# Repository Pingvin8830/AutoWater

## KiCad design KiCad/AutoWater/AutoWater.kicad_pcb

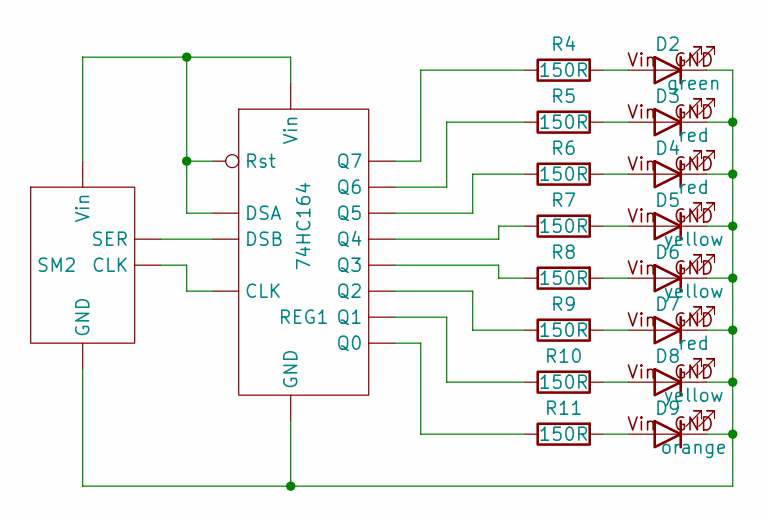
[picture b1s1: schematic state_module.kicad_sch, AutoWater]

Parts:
D2: green; LED 3mm
D3, D4, D7: red; LED 3mm
D5, D6, D8: yellow; LED 3mm
D9: orange; LED 3mm
R4, R5, R6, R7, R8, R9, R10, R11: 150R; Resistor Yageo SMD 1206
REG1: 74HC164; Register 74HC164M SOP-14
SM2: PLS-4

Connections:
unnamed: D2.Vin, R4.2
unnamed: D3.Vin, R5.2
unnamed: D4.Vin, R6.2
unnamed: D5.Vin, R7.2
unnamed: D6.Vin, R8.2
unnamed: D7.Vin, R9.2
unnamed: D8.Vin, R10.2
unnamed: D9.Vin, R11.2
unnamed: R4.1, REG1.Q7
unnamed: R5.1, REG1.Q6
unnamed: R6.1, REG1.Q5
unnamed: R7.1, REG1.Q4
unnamed: R8.1, REG1.Q3
unnamed: R9.1, REG1.Q2
unnamed: R10.1, REG1.Q1
unnamed: R11.1, REG1.Q0
unnamed: REG1.CLK, SM2.3 (CLK)
unnamed: D2.GND, D3.GND, D4.GND, D5.GND, D6.GND, D7.GND, D8.GND, D9.GND, REG1.GND, SM2.4 (GND)
unnamed: REG1.DSB, SM2.2 (SER)
unnamed: REG1.DSA, REG1.Rst, REG1.Vin, SM2.1 (Vin)

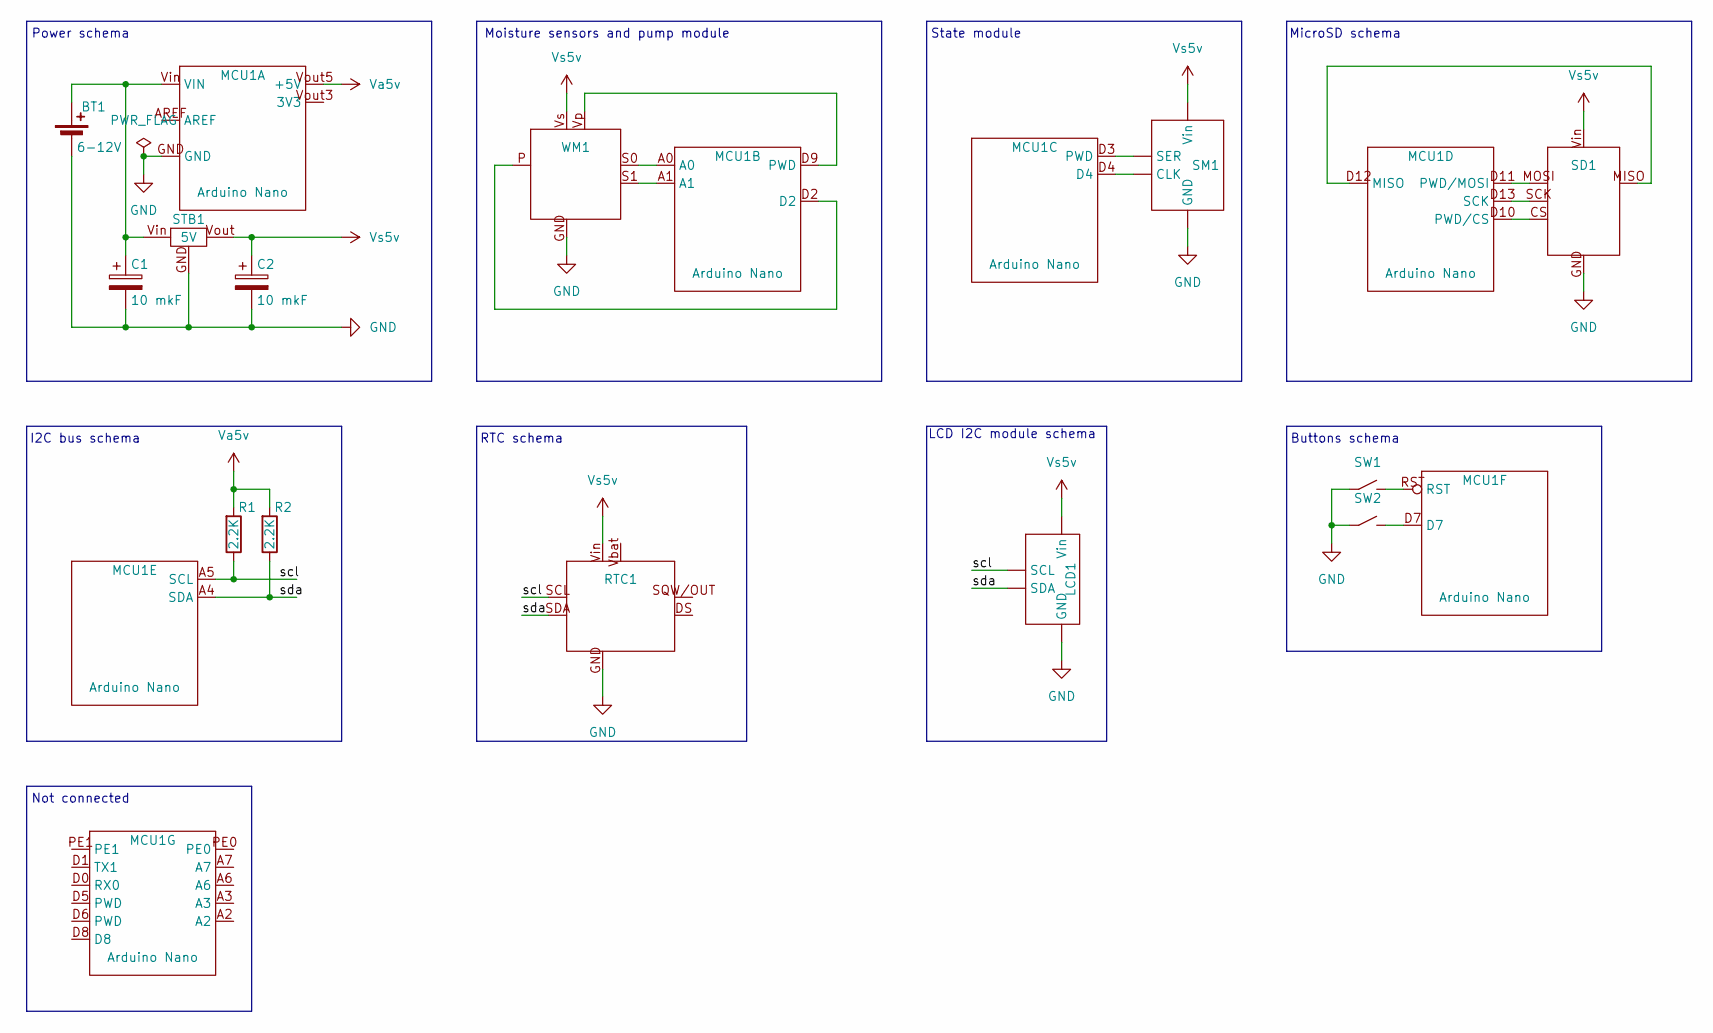
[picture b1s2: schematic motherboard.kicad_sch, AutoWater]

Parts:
BT1: 6-12V; Connector 5.5x2.1 DS-201
C1, C2: 10 mkF; Capacitor Murata SMD 0603
LCD1: LCD I2C module; PLS-4
MCU1: Arduino Nano; Arduino Nano V3 Type C PBS
R1, R2: 2.2K; Resistor Yageo SMD 1206
RTC1: RTC DS1307 module
SD1: MicroSD module
SM1: PLS-4
STB1: 5V; Stabilizer 5V AMS1117-5.0S SMD
SW1, SW2: Button; Connector B2B-XH-A
WM1: PLS-2x3

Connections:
/Motherboard/scl: LCD1.1 (SCL), MCU1.A5 (SCL), R1.1, RTC1.SCL
/Motherboard/sda: LCD1.2 (SDA), MCU1.A4 (SDA), R2.1, RTC1.SDA
GND: BT1.GND (-), C1.GND, C2.GND, LCD1.4 (GND), MCU1.GND, RTC1.GND, SD1.GND, SM1.4 (GND), STB1.GND, SW1.GND (1), SW2.GND (1), WM1.GND
unnamed: BT1.Vout (+), C1.Vin (VCC), MCU1.Vin (VIN), STB1.Vin
unnamed: MCU1.A0, WM1.S0
unnamed: MCU1.A1, WM1.S1
unnamed: MCU1.D2, WM1.P
unnamed: MCU1.D9 (PWD), WM1.Vp
unnamed: MCU1.D3 (PWD), SM1.2 (SER)
unnamed: MCU1.D12 (MISO), SD1.MISO
unnamed: MCU1.D10 (PWD/CS), SD1.CS
unnamed: MCU1.D11 (PWD/MOSI), SD1.MOSI
unnamed: MCU1.D13 (SCK), SD1.SCK
unnamed: MCU1.D4, SM1.3 (CLK)
unnamed: MCU1.RST, SW1.Vin (2)
unnamed: MCU1.D7, SW2.Vin (2)
Va5v: MCU1.Vout5 (+5V), R1.2, R2.2
Vs5v: C2.Vin (VCC), LCD1.3 (Vin), RTC1.Vin, SD1.Vin, SM1.1 (Vin), STB1.Vout, WM1.Vs

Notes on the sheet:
Power schema
LCD I2C module schema
I2C bus schema
Not connected
State module
MicroSD schema
Moisture sensors and pump module
Buttons schema
RTC schema

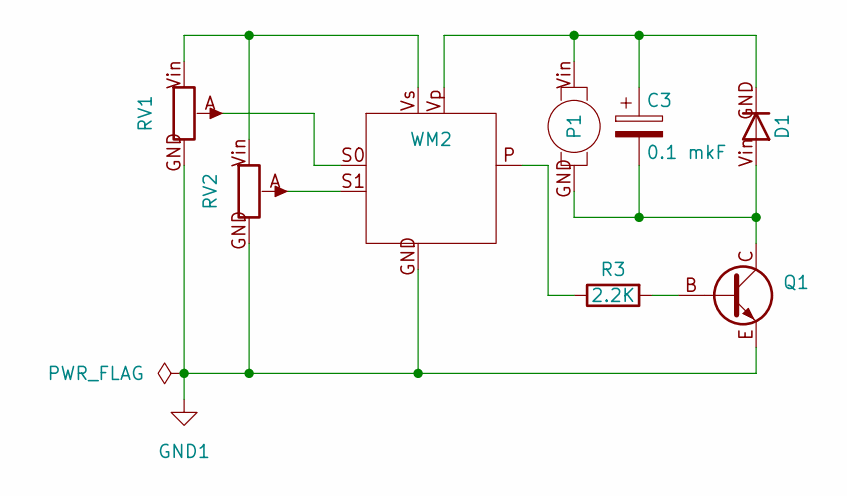
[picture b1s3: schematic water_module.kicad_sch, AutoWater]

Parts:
C3: 0.1 mkF; Capacitor Murata SMD 0402
D1: 1N4001G; DIode 1N4001G THT min
P1: Pump; Connector B2B-XH-A
Q1: BC817-25; NPN transistor BC817-25
R3: 2.2K; Resistor Yageo SMD 1206
RV1, RV2: PLS-3
WM2: PLS-2x3

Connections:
GND1: Q1.E, RV1.GND, RV2.GND, WM2.GND
unnamed: C3.Vin (VCC), D1.GND (K), P1.Vin (VCC), WM2.Vp
unnamed: C3.GND, D1.Vin (A), P1.GND, Q1.C
unnamed: Q1.B, R3.2
unnamed: R3.1, WM2.P
unnamed: RV1.A, WM2.S0
unnamed: RV1.Vin (VCC), RV2.Vin (VCC), WM2.Vs
unnamed: RV2.A, WM2.S1

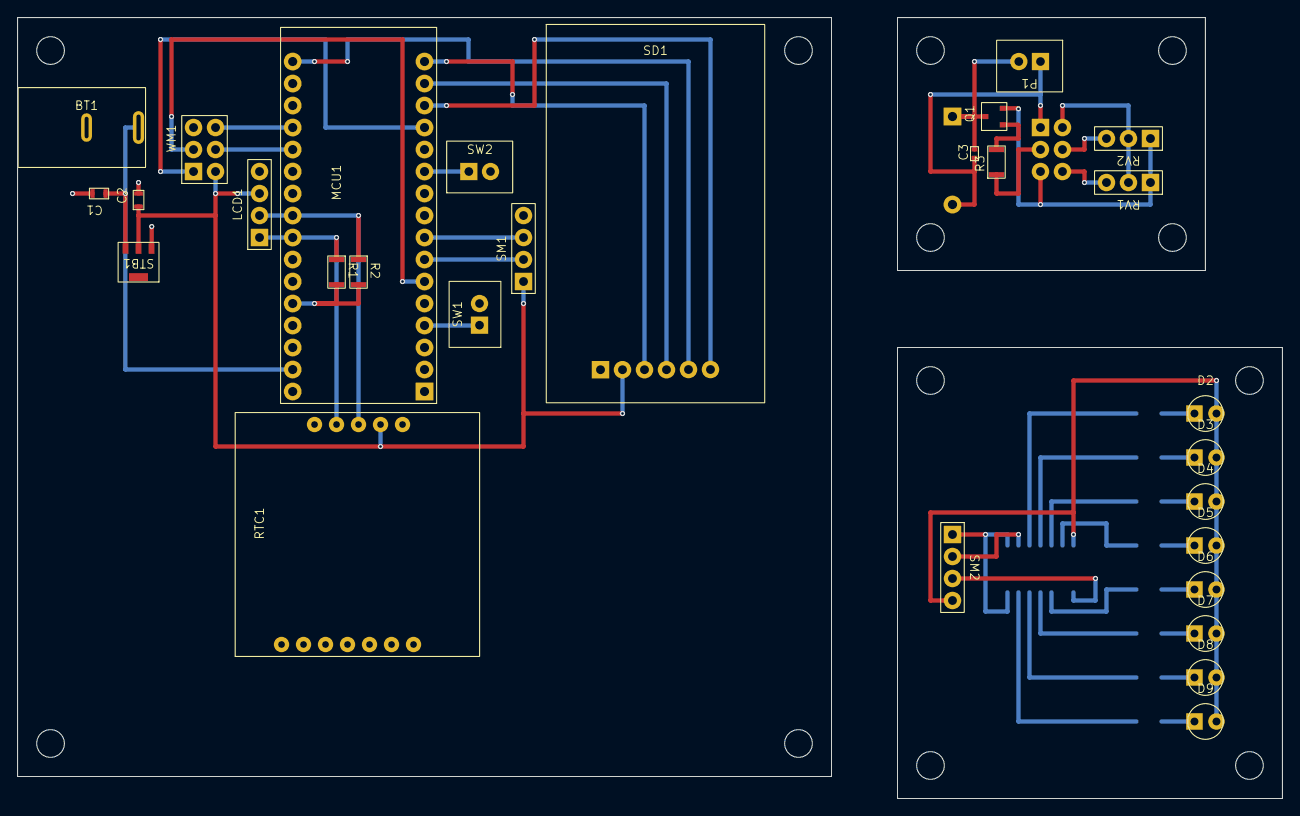
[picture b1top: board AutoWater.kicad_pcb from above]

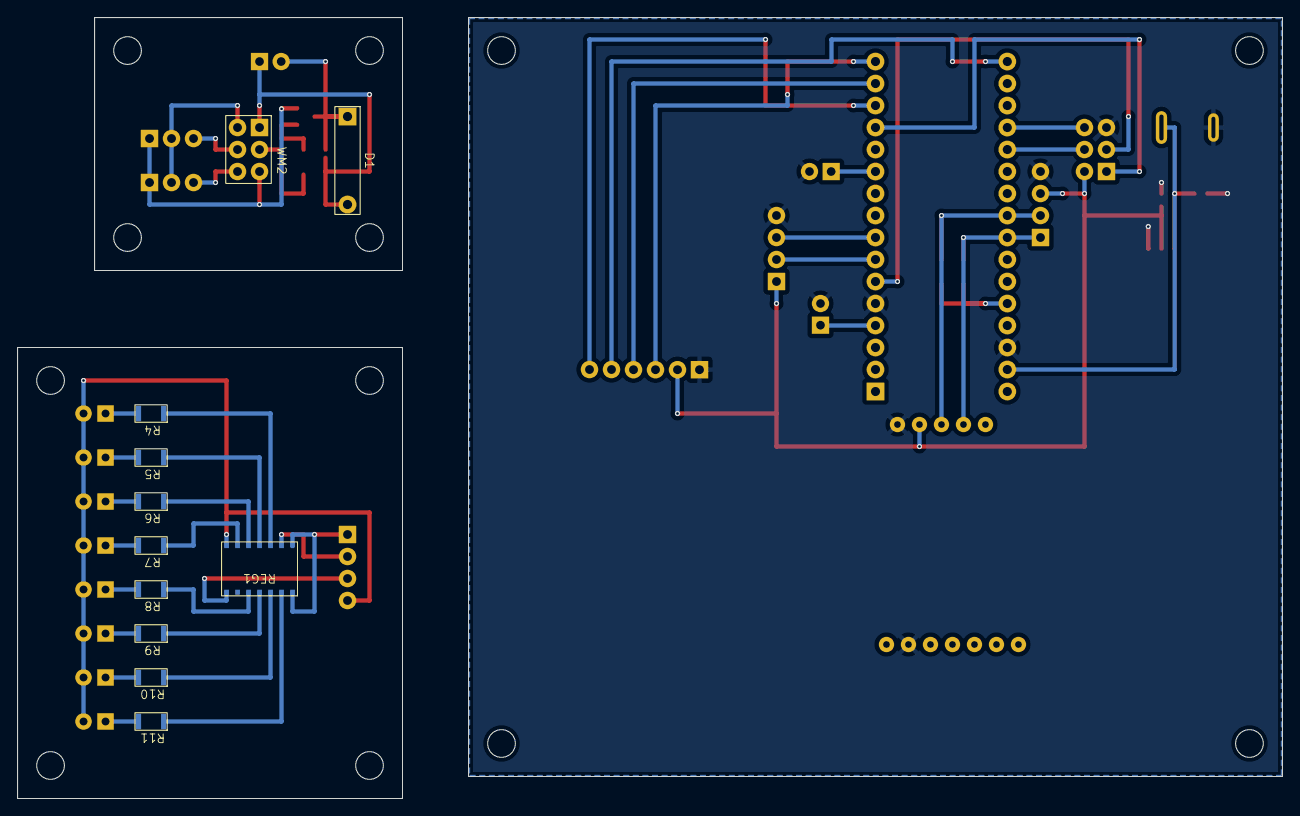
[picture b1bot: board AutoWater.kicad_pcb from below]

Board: 2 copper layers, 146.0 x 90.2 mm, 40 parts (11 on the bottom side), 46 nets.

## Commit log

2026-01-09 Add hardware list
2026-01-09 Add rele in hardware list
2026-01-09 Add connections list
2026-01-09 Create sketch
2026-01-09 Remove RTCEnabled, use state. Add check RTC every day
2026-01-09 Add show state
2026-01-09 Add SD state in state, remove SDEnabled
2026-01-09 Add init sensors
2026-01-09 Add logic 2 sensor
2026-01-09 Add write values
2026-01-09 Fix time to write values
2026-01-12 Rewrite
2026-01-12 Add plans
2026-01-15 Create log parser
2026-01-15 Add state register
2026-01-15 Create KiCad project
2026-01-17 Create electric schema
2026-01-17 Add nominals
2026-01-17 Replace I2C resisters
2026-01-18 Create layout placed
2026-01-18 Electric checks
2026-01-18 Add power symbols
2026-01-19 Refactoring schema
2026-01-19 Recreate specification
2026-01-19 Ooops
2026-01-19 Clearing
2026-01-21 Rename to Full
2026-01-21 Back
2026-01-23 Refactor RTC to module
2026-01-23 Create layouts
